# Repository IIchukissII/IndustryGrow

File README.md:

<!--
SPDX-FileCopyrightText: 2026 The IndustryGrow contributors
SPDX-License-Identifier: CC-BY-SA-4.0
-->

<picture>
  <source media="(prefers-color-scheme: dark)" srcset="img/industrygrow-logo-mono-dark.svg" />
  
</picture>

# IndustryGrow

Open-core field hardware, firmware and edge software for instrumented, profile-driven crop
cultivation. One architecture, from a cabinet to a several-hundred-square-metre facility. The
companion platform **IndustryFlow** stores history, runs analytics and distributes profiles.

Scope and rationale: [`MOTIVATION.md`](MOTIVATION.md), [ADR-0001](ADR/ADR-0001-industrygrow-as-an-open-core-cultivation-platform-on-industryflow.md).

## Architecture constraints

| Constraint | Record |
|---|---|
| Scaling multiplies node *instances* across zones. It adds no node classes. | ADR-0014 |
| A signed, versioned JSON cultivation profile is the only channel that changes deployment behaviour. There is no remote-command API and no real-time tuning channel. | ADR-0015, ADR-0025 |
| The gateway runs control loops locally against a cached profile. The cloud supplies profiles and observes; it does not command in real time. | ADR-0015, ADR-0004 |
| The over-temperature trip is analog, MCU- and bus-independent, and sits at the heating actuator. Profiles set operating parameters; hardware sets survival parameters. | ADR-0018 |
| Sensor density is a deployment phase, not a fixture: dense during the empirical survey, reduced for the operating phase. The profile carries the identified model with the setpoints. | ADR-0016 |

## Technology

| Layer | Choice |
|---|---|
| Field bus | Cyphal over classic CAN @ 500 kbit/s, linear topology |
| Smart-node MCU | WeAct STM32F4 64-pin core board (STM32F405RGT6; F412/F446 drop-in) |
| Node carrier PCB | Custom integration board: CAN transceiver, ATECC608 secure element, two-header sensor-module interface |
| Node firmware | Embedded C with libcanard. One application holds every module personality; the module-ID strap selects at boot |
| Node flash layout | Bootloader at the reset vector plus the application in one of two slots; build output is `igrowboot.hex`, `igrow-a.hex`, `igrow-b.hex` |
| Firmware update | Signed image served over the bus, `uavcan.file.Read` to the slot that is not running, trial boot with fallback |
| Gateway | Raspberry Pi (3B+ minimum, 4/5 for higher traffic) + isolated 2-channel CAN HAT |
| Gateway software | Python / asyncio, SocketCAN + Pycyphal + Nunavut-generated DSDL bindings |
| Cloud link | mTLS to IndustryFlow; stateless edge in steady state, with a bounded local store for buffering and survey |
| Identity | Module class from the ID strap, `unique_id` from the ATECC608, Node-ID from a carrier-resident store; 127 = unprovisioned |
| Security | Operator CA, signed firmware, signed profiles |

Governing records: ADR-0002 (bus, carrier, gateway), ADR-0005 (DSDL), ADR-0020
(persistence), ADR-0027 (identity), ADR-0029 (update and bootloader), ADR-0024 / ADR-0025 (CA,
profile signing).

> PCBs are authored in **KiCad 10** and will not open in earlier versions; cabinet distribution
> schematics (`E0007`) use **QElectroTech**. Design files live in `store/` under the ADR-0017
> scheme, packaged per document layer as `Exxxx-VVVVVV-S-src.zip` / `-D-src.zip` (d19).
> [`CONTRIBUTING.md`](CONTRIBUTING.md) has the unpack/repack procedure.

## Hardware

Seven sensor-module classes (M01–M07), one functional subsystem each, on the universal carrier
`E0001`, in the cabinet distribution case `E0007`. Instances of one design are specialized by
populated BOM, never by new designs; a functional group fitted or omitted at build is a populate
variant with its own assembly E-number (ADR-0017).

E-numbers, sensor complement, module-ID straps, variant rules and per-design state:
[`REGISTRY.md`](REGISTRY.md).

## Status

Phase 1 is data collection only, no actuators; it ends at stage 4, full cabinet telemetry from
M01–M05. Stage sequencing, dependencies, the Phase 1 → Phase 2 boundary and the v1.0 exit
criteria: [`project/ROADMAP.md`](project/ROADMAP.md), 14 dependency-ordered stages.

## Repository

| Path | Contents | Records |
|---|---|---|
| [`ADR/`](ADR/) | Architecture decision records — the source of truth — plus [`GLOSSARY.md`](ADR/GLOSSARY.md) | ADR-0000 |
| [`docs/`](docs/) | Decision manuals: how an ADR is realised and the code that realises it | — |
| [`REGISTRY.md`](REGISTRY.md) | E-number / SP-number identifier map, machine-readable | ADR-0017, ADR-0019, ADR-0023 |
| [`store/`](store/) | Hardware design sources, fab packages and firmware release artifacts, flat, keyed by identifier | ADR-0017 |
| [`spec/`](spec/) | Module specifications — M01, M02, M05, M06, M07. M03 and M04 not yet written | ADR-0014 |
| [`firmware/`](firmware/) | Node firmware (C, libcanard) and the `industryflow.greenhouse` DSDL vocabulary | ADR-0005, ADR-0029 |
| [`gateway/`](gateway/) | Gateway provisioning, hardening, identity and profile-pull client | ADR-0004, ADR-0015 |
| [`erp/`](erp/) | Instance-and-integration ERP — the pre-cloud system of record | ADR-0021, ADR-0022 |
| [`pki/`](pki/) | Operator CA bootstrap and root-key ceremony | ADR-0024 |
| [`signing/`](signing/) | Profile signing tool and runbook | ADR-0025 |
| [`profiles/`](profiles/) | Cultivation profile instances | ADR-0003 |
| [`project/`](project/) | `ROADMAP.md` stage plan, `RESEARCH.md` open directions L1–L7 | — |
| [`MOTIVATION.md`](MOTIVATION.md) | The gap this project closes | — |
| [`CONTRIBUTING.md`](CONTRIBUTING.md) | Contribution licensing, DCO sign-off, working with the store | — |

## Build and run

Firmware — three images, ARM cross-toolchain and Ninja required:

```sh
firmware/tools/bootstrap.sh            # pin submodules; needs nnvg (Nunavut)
cmake -S firmware -B firmware/build -G Ninja \
      -DCMAKE_MAKE_PROGRAM="$(command -v ninja)" \
      -DCMAKE_TOOLCHAIN_FILE="$PWD/firmware/cmake/arm-none-eabi.cmake"
cmake --build firmware/build
```

ERP — application plus operator console:

```sh
cd erp && docker compose up --build    # app on 127.0.0.1:8021
```

Gateway — runs on the Pi, post-first-boot, idempotent:

```sh
sudo ./provision.sh                    # from the staged gateway/ bundle
```

Per-component detail, flashing procedure and signing keys are in each directory's `README.md`.

## Licensing

Open-core, licensed per part of the repository. [`LICENSE.md`](LICENSE.md) is the authoritative
mapping — hardware designs, documentation, application code and the DSDL protocol layer carry four
different licences, and directory-level assumptions do not hold. Full texts are in
[`LICENSES/`](LICENSES/).

Third-party content keeps its own terms, annotated in [`REUSE.toml`](REUSE.toml): the WeAct
core-board snapshot is published with **no licence stated**, so it is not covered by this project's
licences. Compliance is CI-enforced — run `reuse lint` before opening a pull request.

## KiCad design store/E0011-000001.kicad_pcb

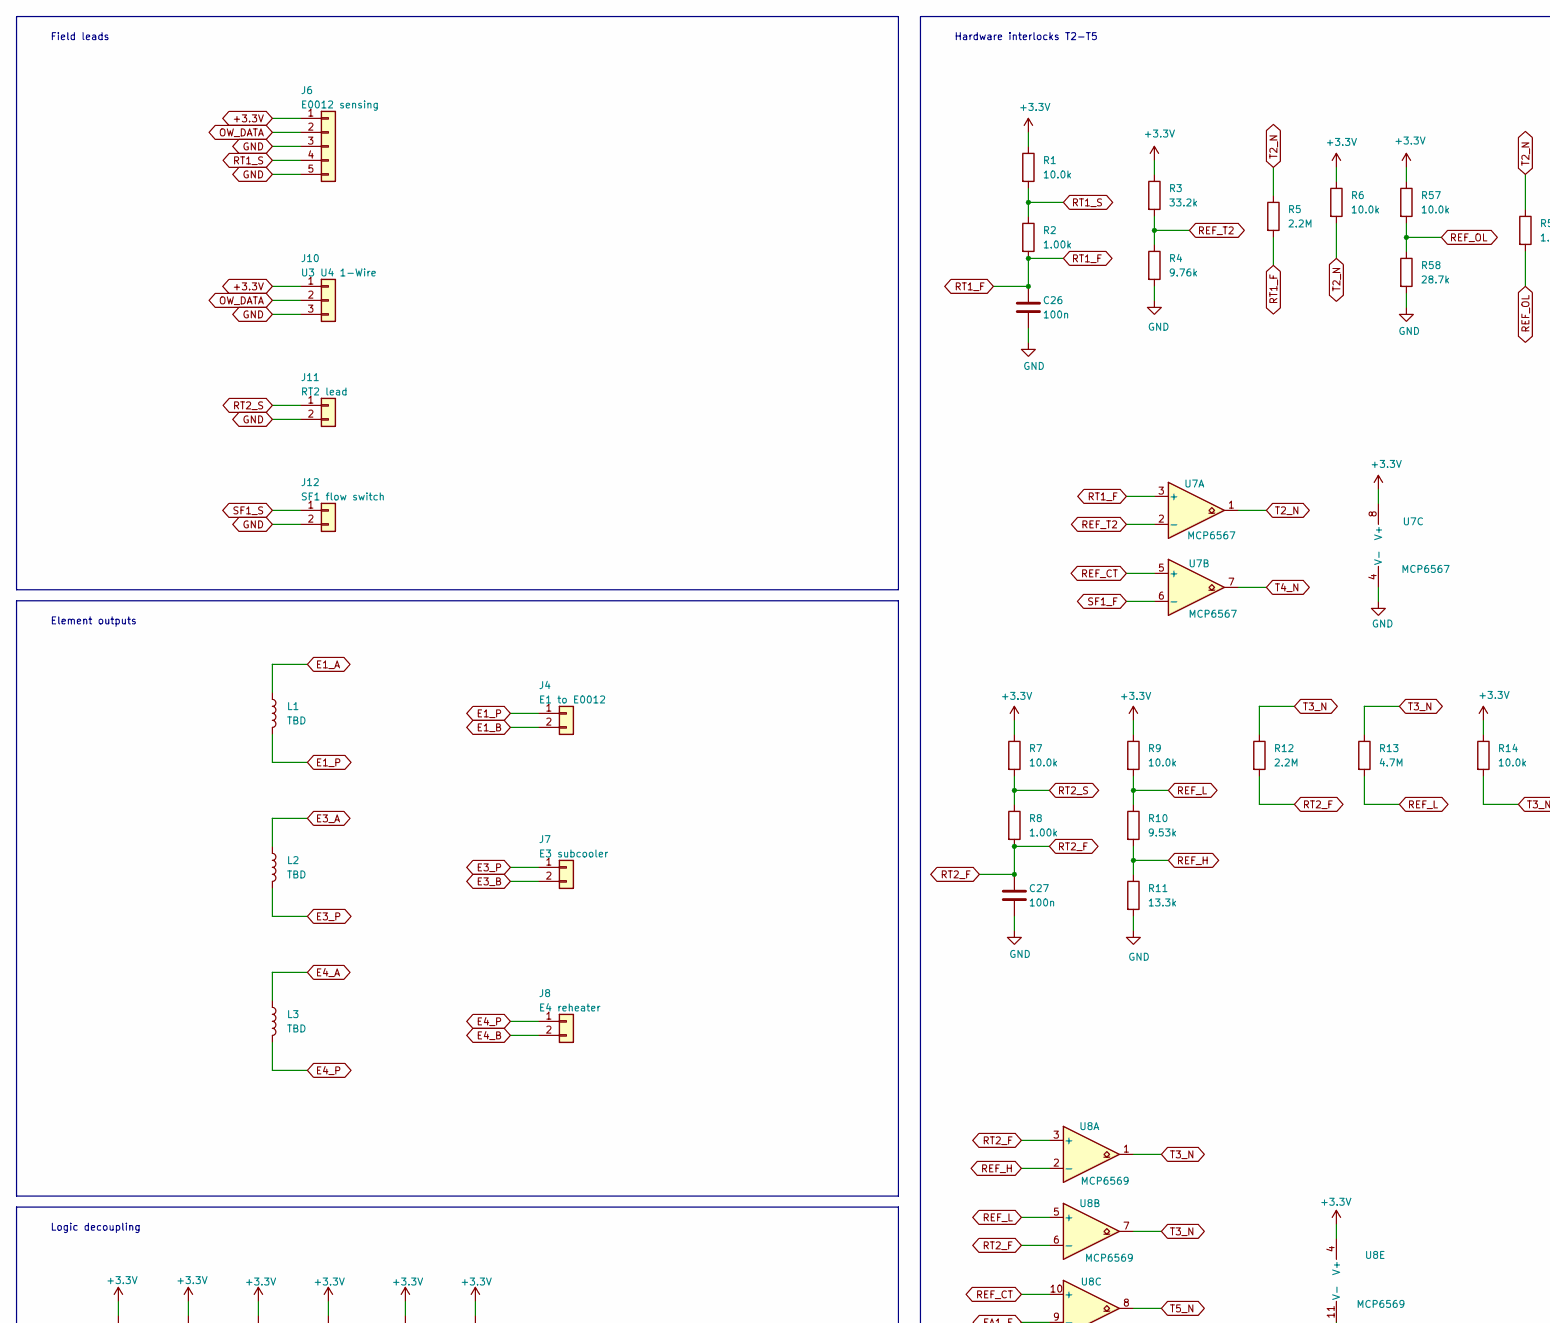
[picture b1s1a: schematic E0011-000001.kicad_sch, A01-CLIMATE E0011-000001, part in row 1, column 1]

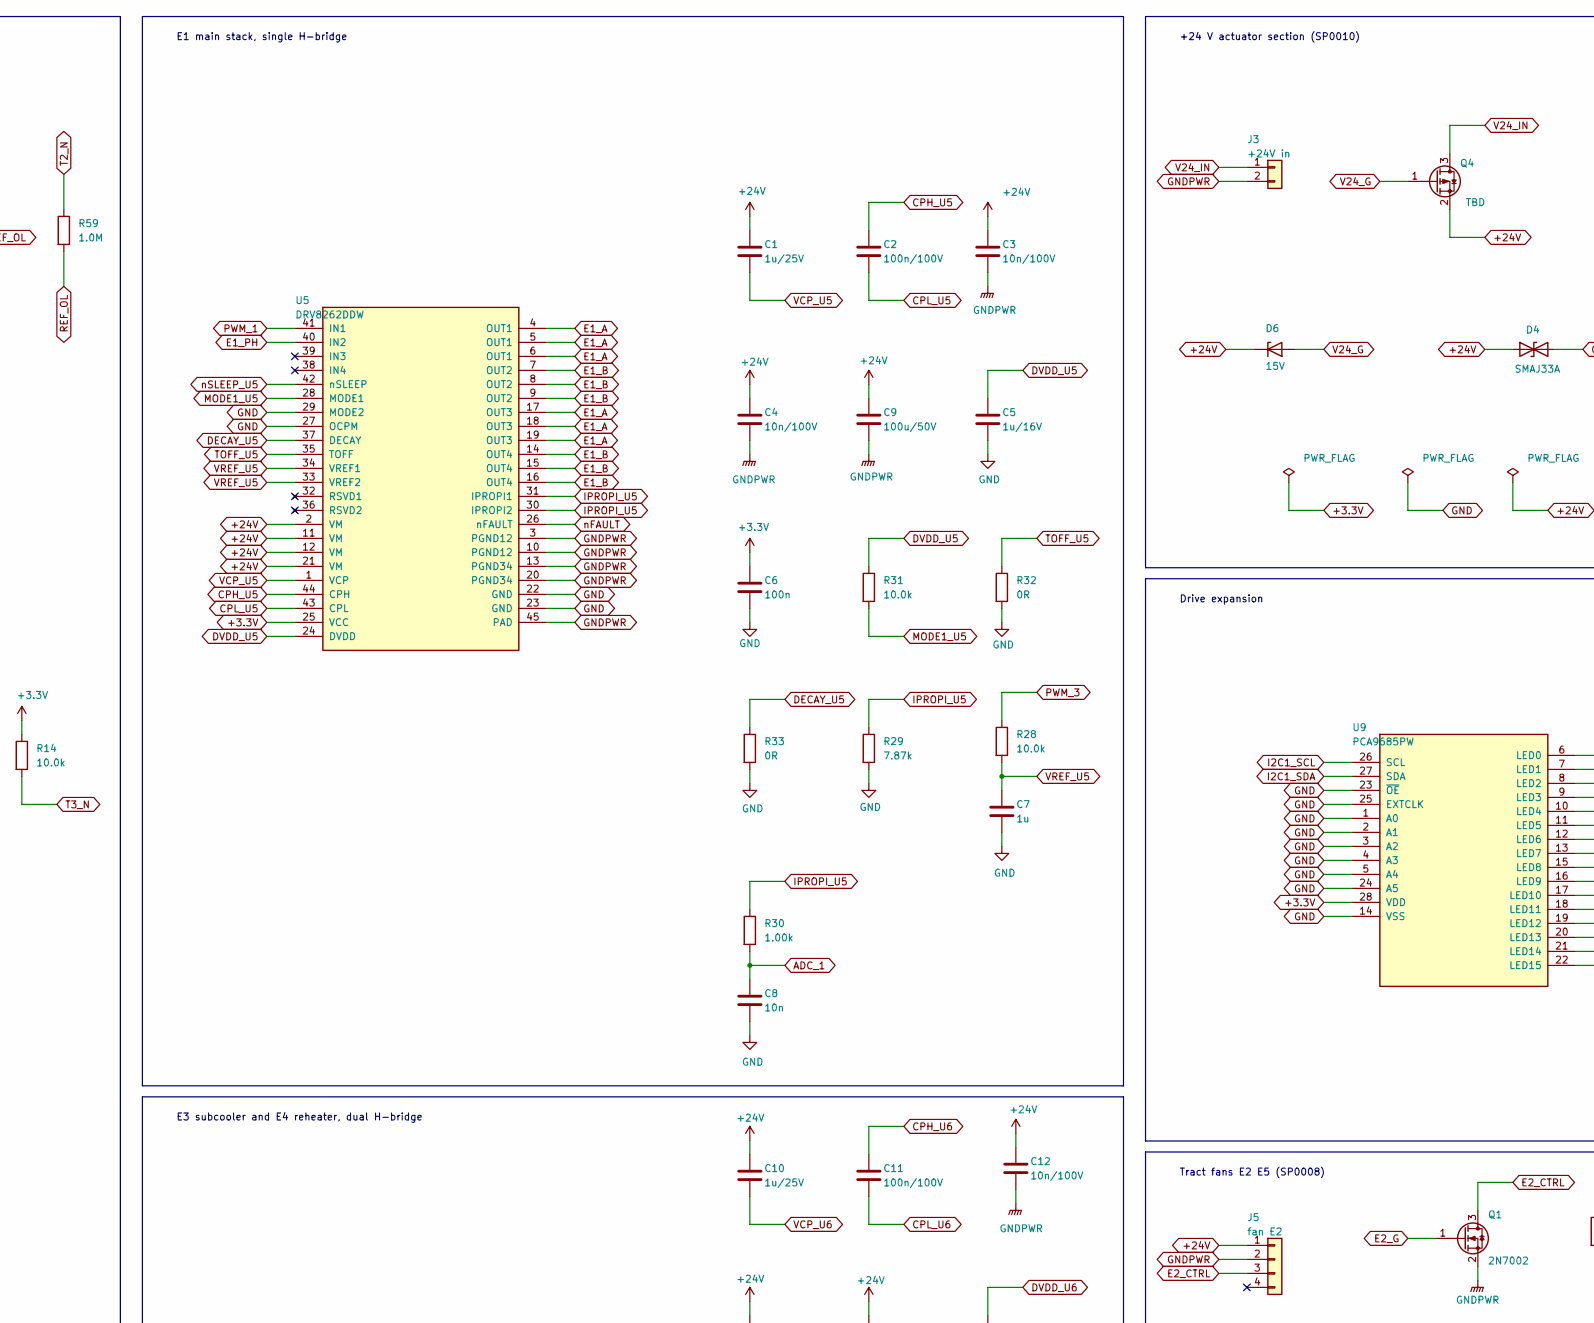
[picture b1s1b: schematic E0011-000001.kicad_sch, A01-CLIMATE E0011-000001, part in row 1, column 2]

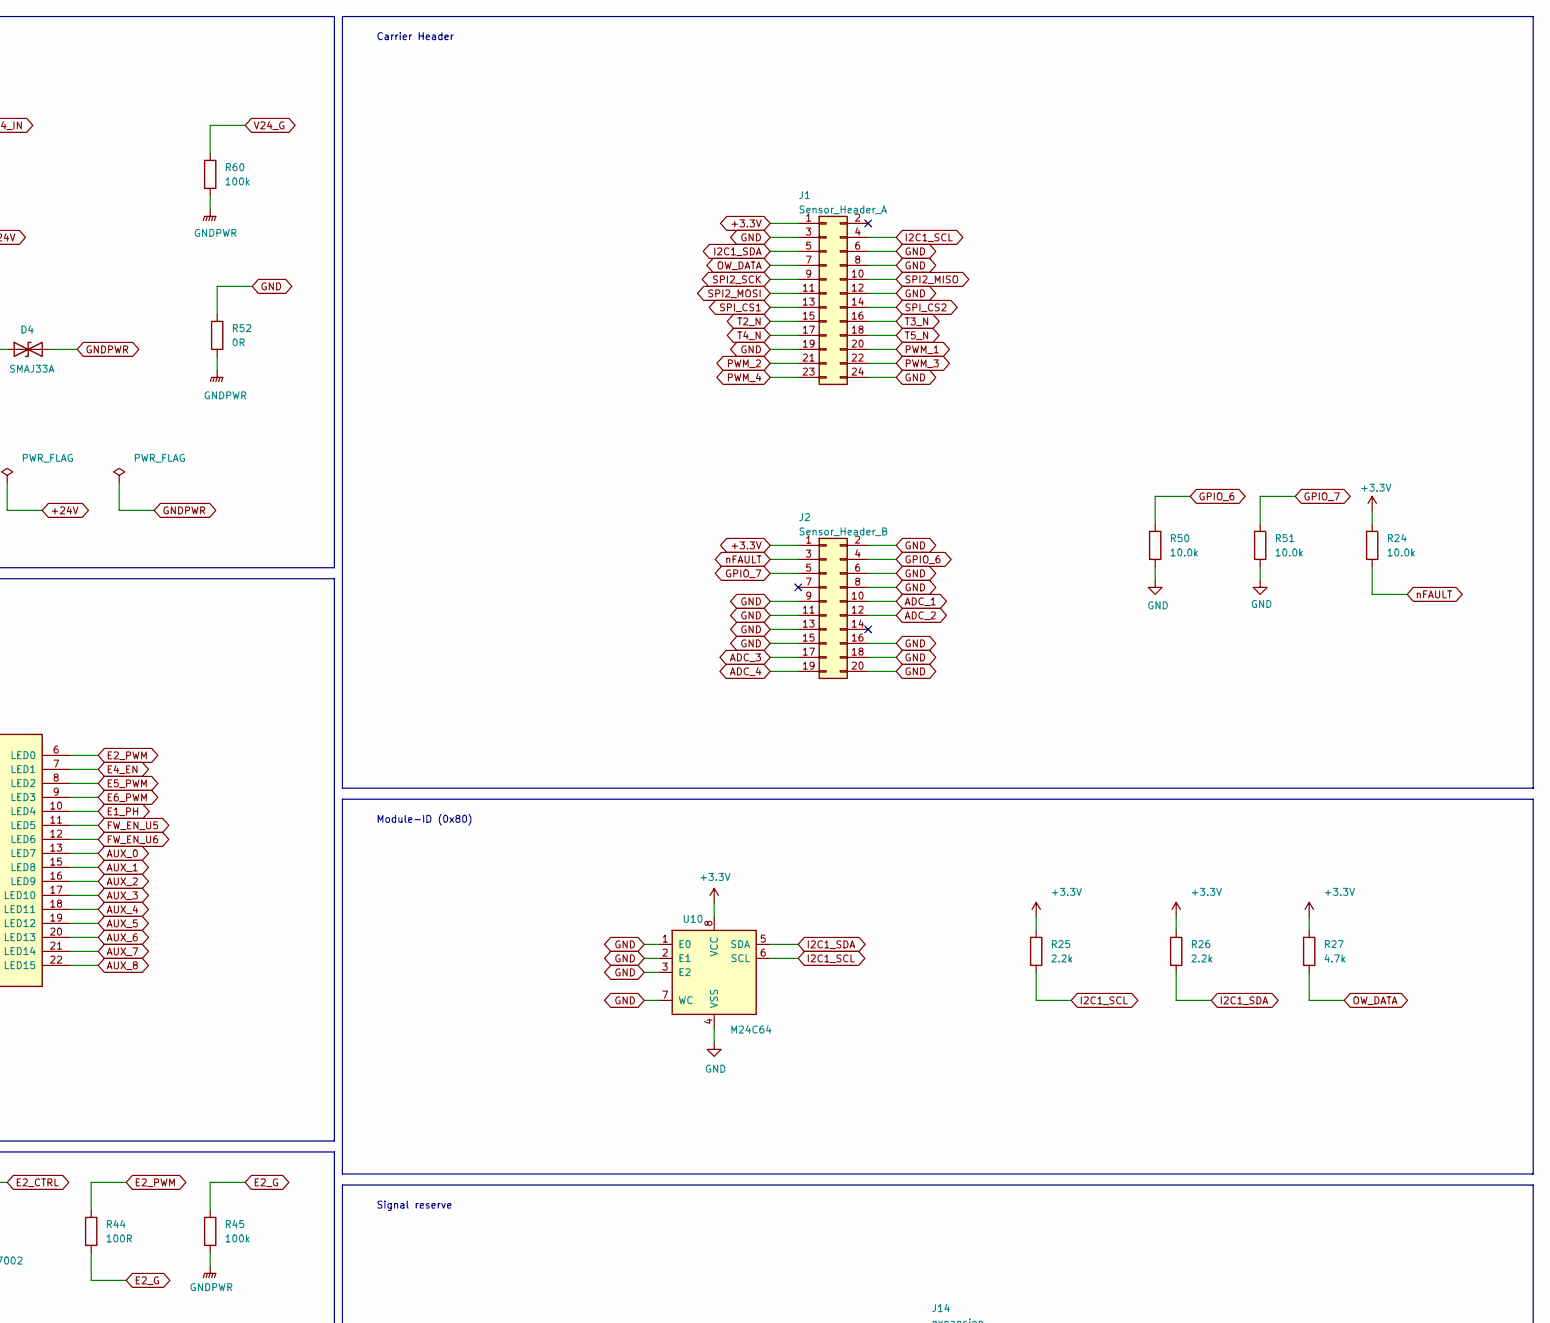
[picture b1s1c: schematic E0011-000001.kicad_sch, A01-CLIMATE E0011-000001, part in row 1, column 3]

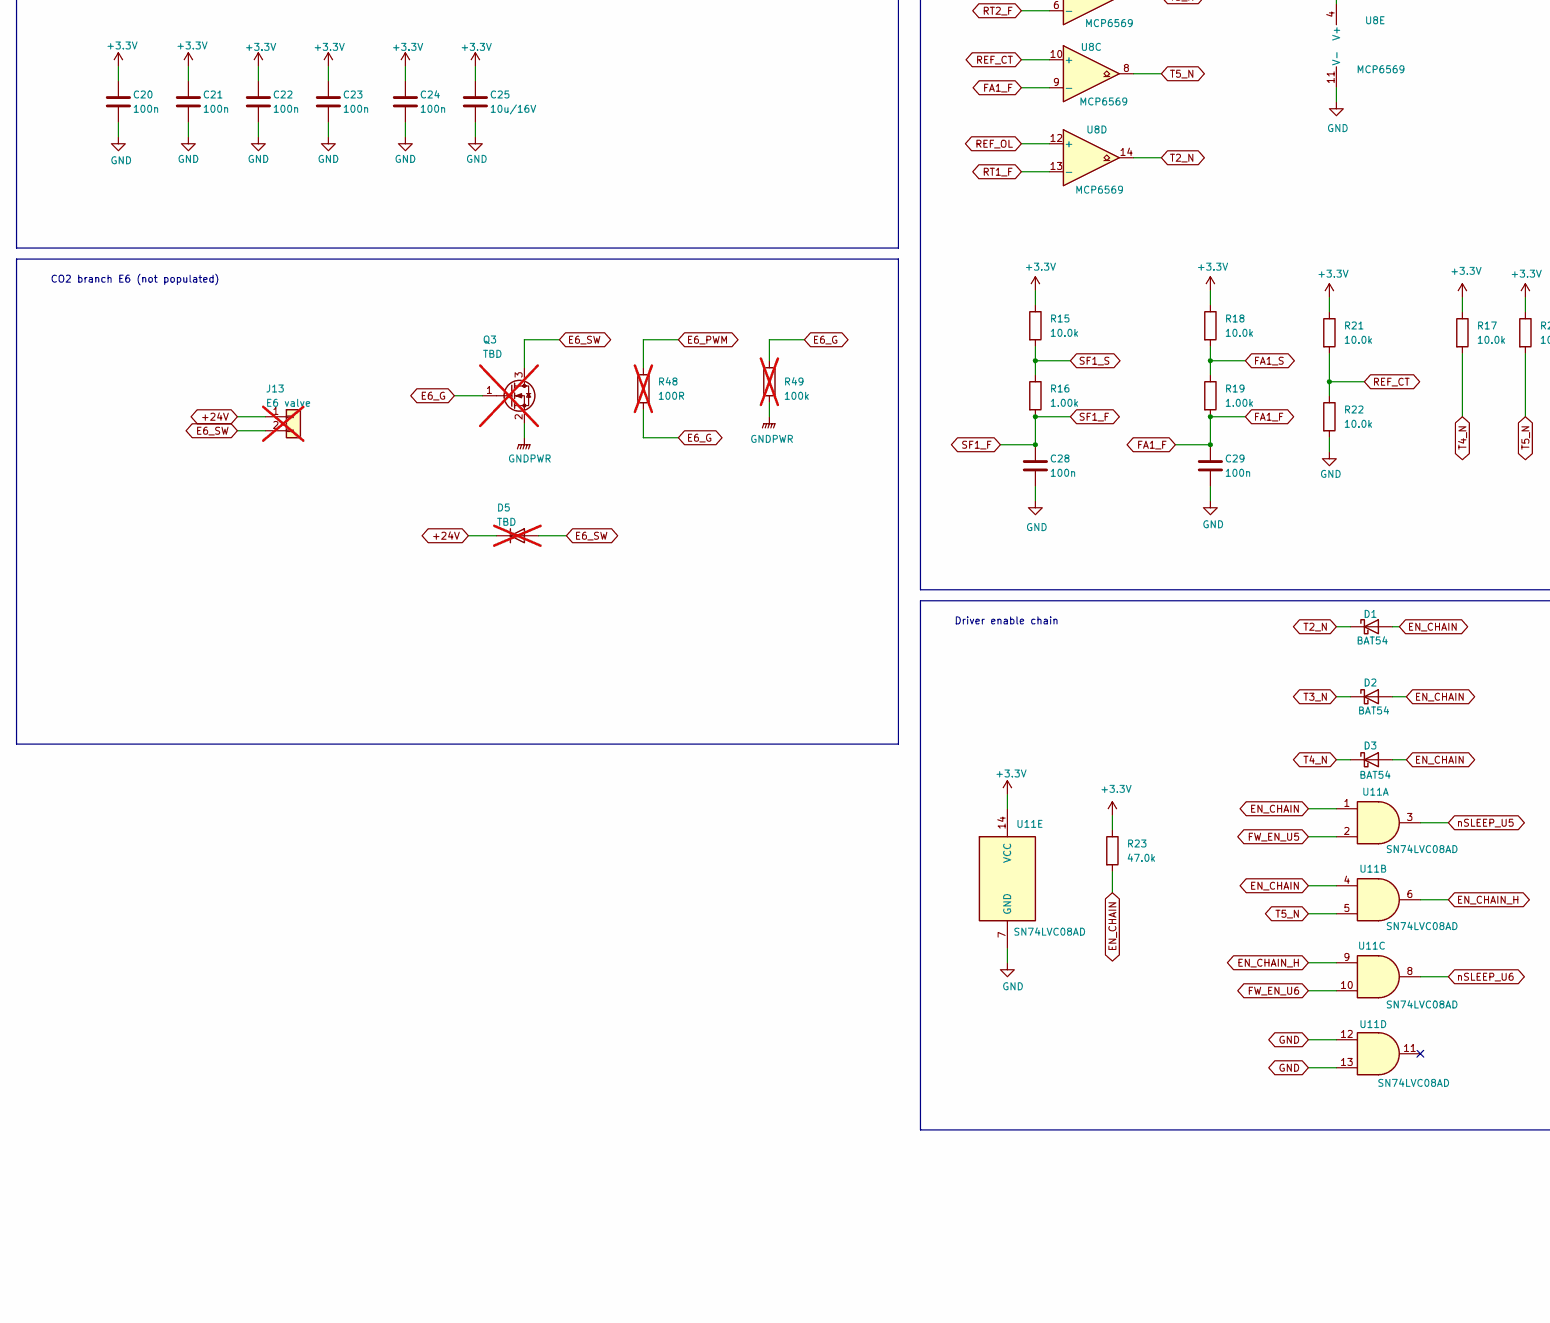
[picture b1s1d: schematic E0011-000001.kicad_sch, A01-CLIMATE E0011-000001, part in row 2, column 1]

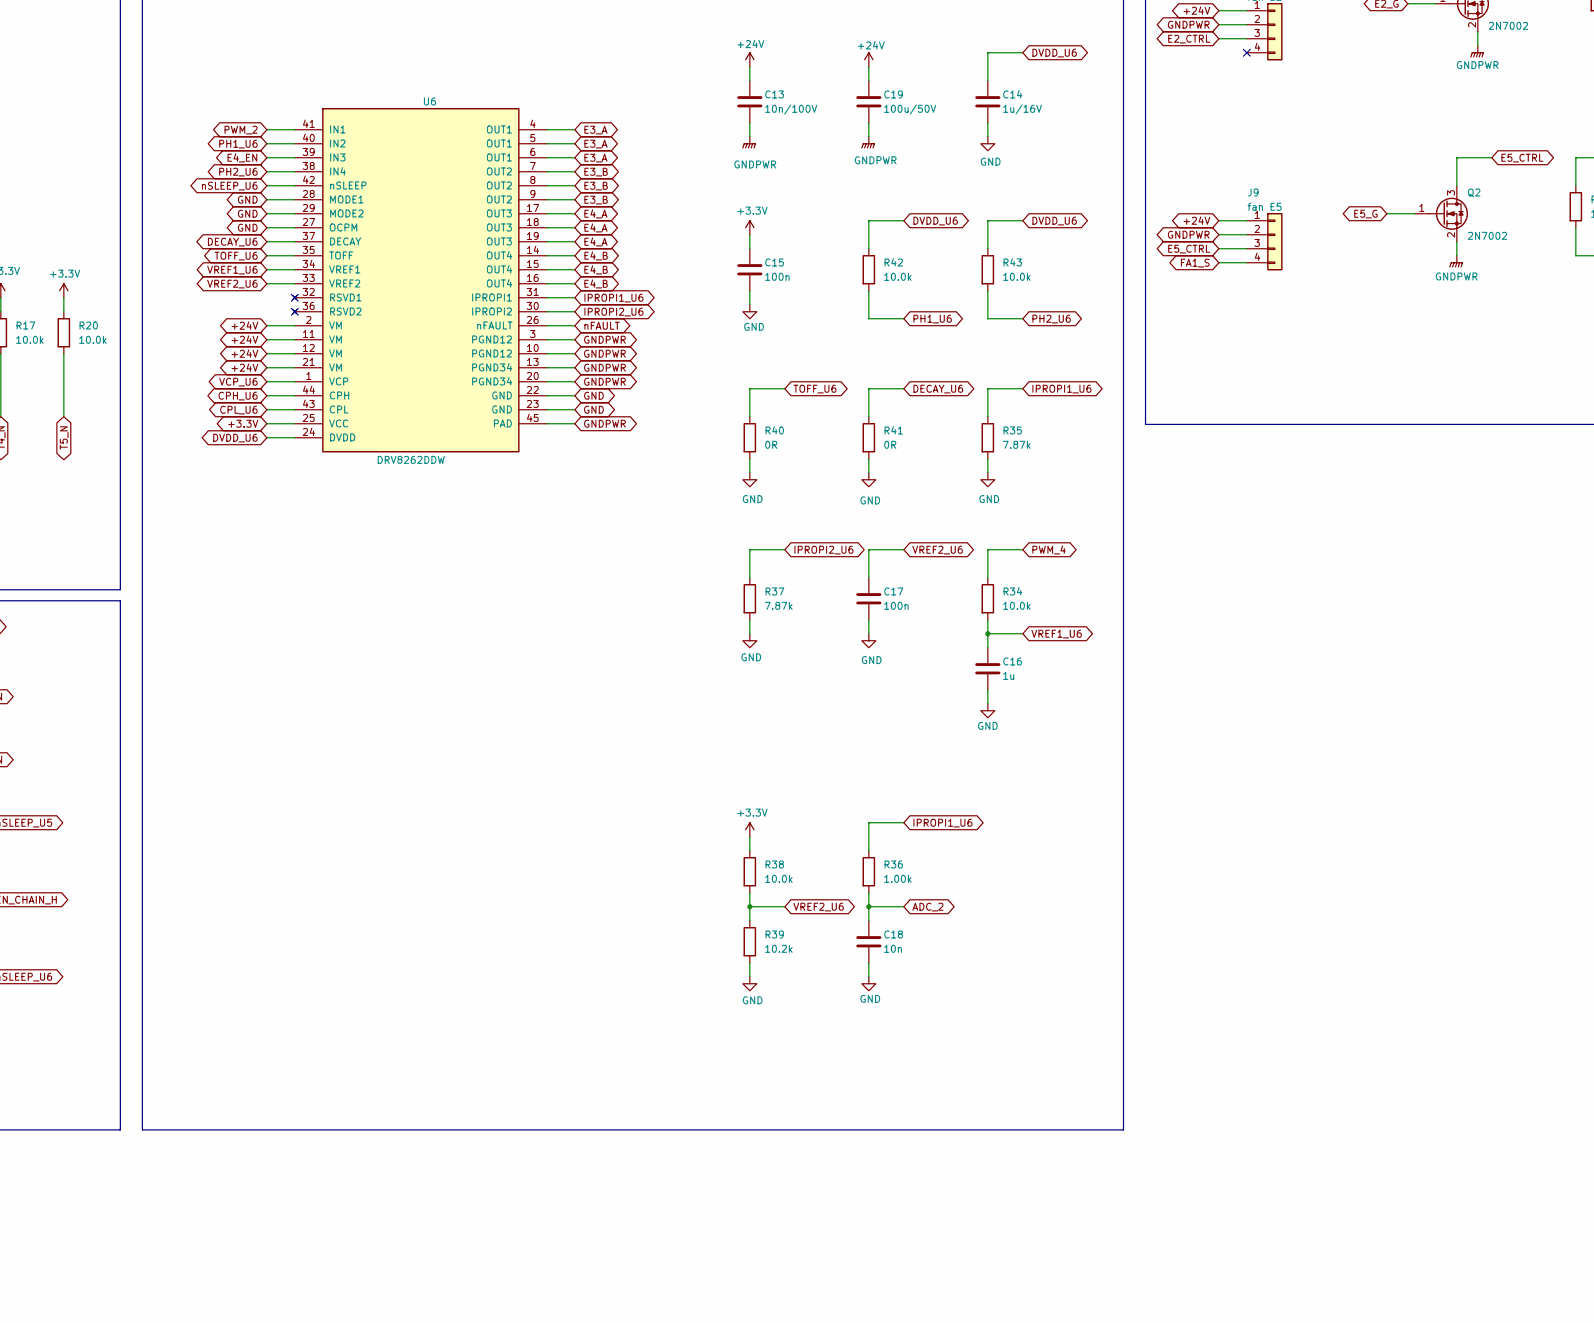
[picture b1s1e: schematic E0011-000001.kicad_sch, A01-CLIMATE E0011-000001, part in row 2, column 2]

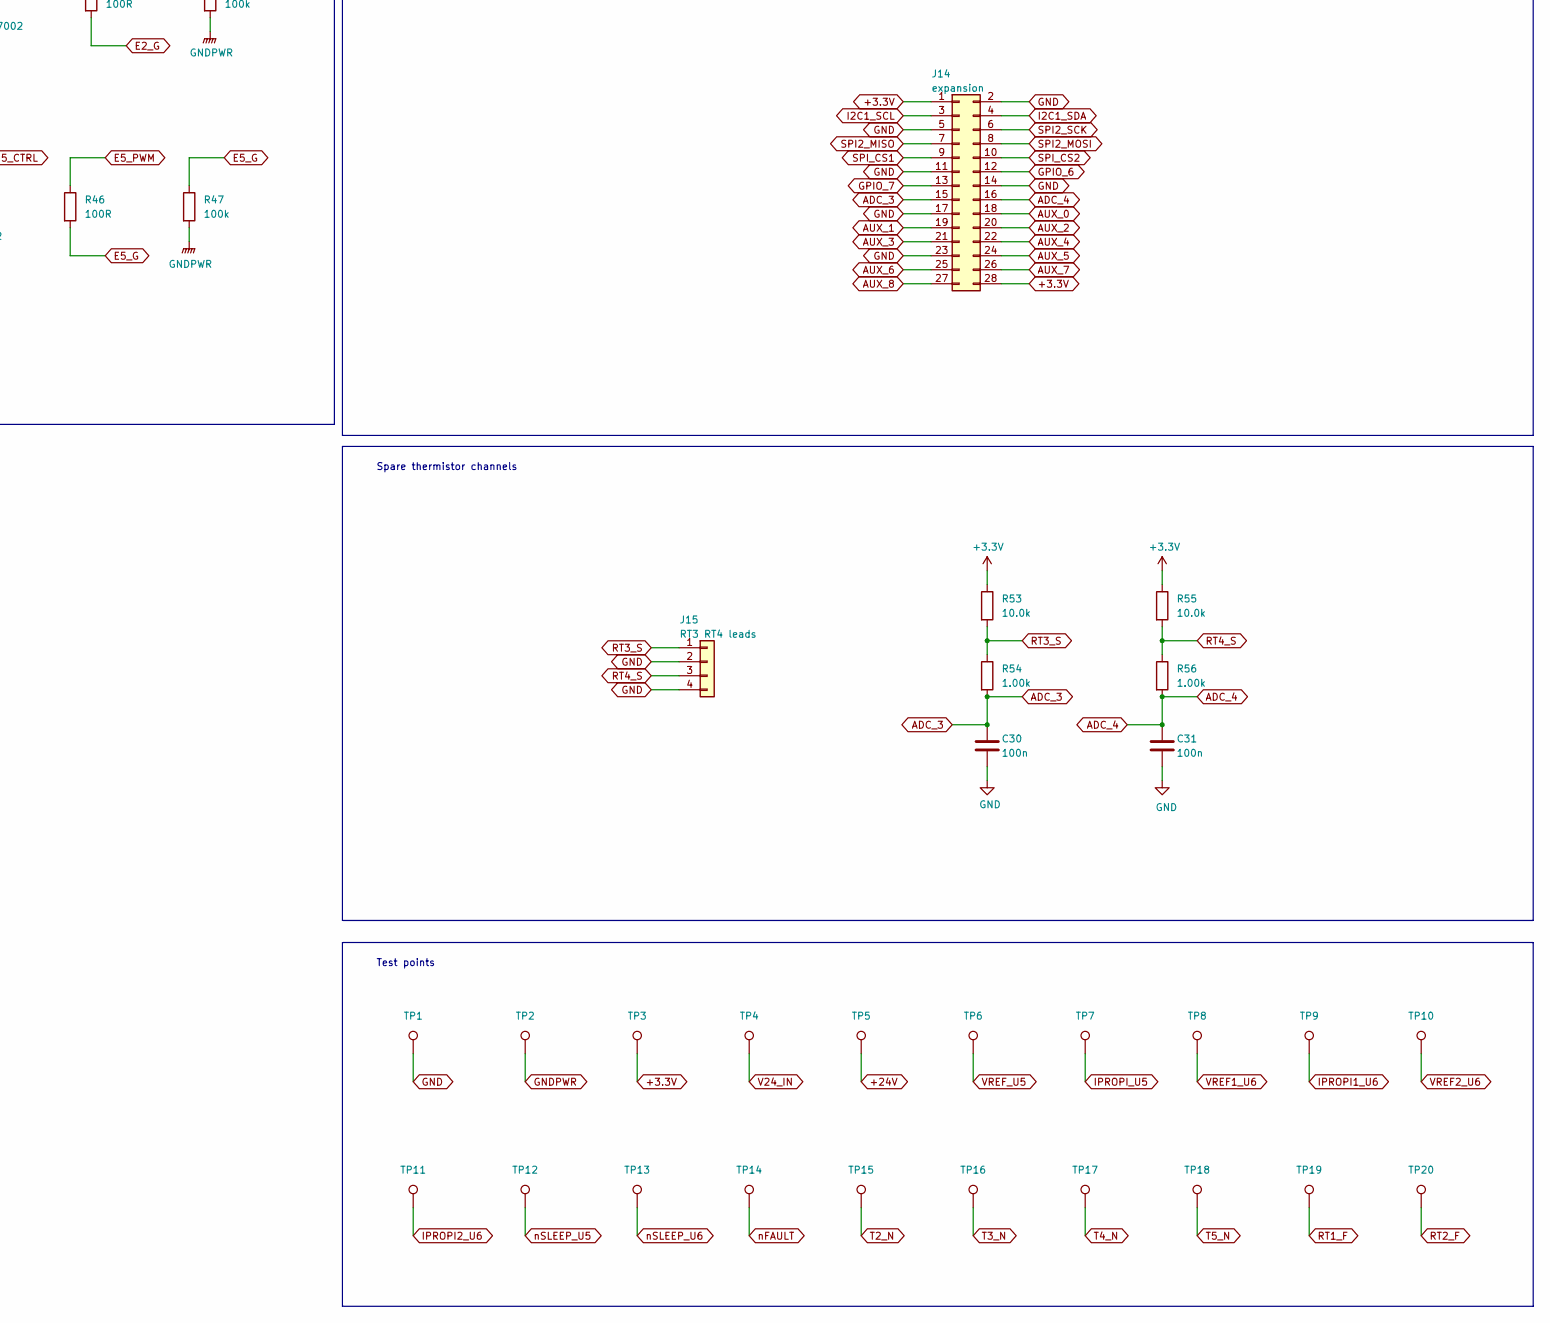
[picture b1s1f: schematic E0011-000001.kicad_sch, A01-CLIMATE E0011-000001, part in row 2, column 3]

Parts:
C1, C10: 1u/25V; C_0805_2012Metric
C2: 100n/100V; C_0805_2012Metric
C3, C4, C12, C13: 10n/100V; C_0805_2012Metric
C5, C14: 1u/16V; C_0805_2012Metric
C6, C15, C17, C20, C21, C22, C23, C24, C26, C27, C28, C29, C30, C31: 100n; C_0805_2012Metric
C7, C16: 1u; C_0805_2012Metric
C8, C18: 10n; C_0805_2012Metric
C9, C19: 100u/50V; CP_Elec_8x10.5
C11: 100n/100V; C_0603_1608Metric
C25: 10u/16V; C_0805_2012Metric
D1, D2, D3: BAT54; D_SOD-123
D4: SMAJ33A; D_SMA
D5: TBD; D_SOD-123; not fitted
D6: 15V; D_SOD-123
J1: Sensor_Header_A; PinHeader_2x12_P2.54mm_Vertical
J2: Sensor_Header_B; PinHeader_2x10_P2.54mm_Vertical
J3: +24V in; TerminalBlock_Phoenix_MKDS-1,5-2_1x02_P5.00mm_Horizontal
J4: E1 to E0012; TerminalBlock_Phoenix_MKDS-1,5-2_1x02_P5.00mm_Horizontal
J5: fan E2; Molex_Micro-Fit_3.0_43650-0400_1x04_P3.00mm_Horizontal
J6: E0012 sensing; Molex_Micro-Fit_3.0_43650-0500_1x05_P3.00mm_Horizontal
J7: E3 subcooler; TerminalBlock_Phoenix_MKDS-1,5-2_1x02_P5.00mm_Horizontal
J8: E4 reheater; TerminalBlock_Phoenix_MKDS-1,5-2_1x02_P5.00mm_Horizontal
J9: fan E5; Molex_Micro-Fit_3.0_43650-0400_1x04_P3.00mm_Horizontal
J10: U3 U4 1-Wire; Molex_Micro-Fit_3.0_43650-0300_1x03_P3.00mm_Horizontal
J11: RT2 lead; Molex_Micro-Fit_3.0_43650-0200_1x02_P3.00mm_Horizontal
J12: SF1 flow switch; Molex_Micro-Fit_3.0_43650-0200_1x02_P3.00mm_Horizontal
J13: E6 valve; TerminalBlock_Phoenix_MKDS-1,5-2_1x02_P5.00mm_Horizontal; not fitted
J14: expansion; PinHeader_2x14_P2.54mm_Vertical
J15: RT3 RT4 leads; Molex_Micro-Fit_3.0_43650-0400_1x04_P3.00mm_Horizontal
L1, L2, L3: TBD; L_12x12mm_H8mm
Q1, Q2: 2N7002; SOT-23
Q3: TBD; SOT-23; not fitted
Q4: TBD; SOT-23
R1, R6, R7, R9, R14, R15, R17, R18, R20, R21, R22, R24, R28, R43, R50, R51, R53, R55, R57: 10.0k; R_0805_2012Metric
R2, R8, R16, R19, R54, R56: 1.00k; R_0805_2012Metric
R3: 33.2k; R_0805_2012Metric
R4: 9.76k; R_0805_2012Metric
R5, R12: 2.2M; R_0805_2012Metric
R10: 9.53k; R_0805_2012Metric
R11: 13.3k; R_0805_2012Metric
R13: 4.7M; R_0805_2012Metric
R23: 47.0k; R_0805_2012Metric
R25, R26: 2.2k; R_0805_2012Metric
R27: 4.7k; R_0805_2012Metric
R29, R35, R37: 7.87k; R_0603_1608Metric
R30, R36: 1.00k; R_0603_1608Metric
R31, R34, R38, R42: 10.0k; R_0603_1608Metric
R32, R33, R40, R41: 0R; R_0603_1608Metric
R39: 10.2k; R_0603_1608Metric
R44, R46: 100R; R_0805_2012Metric
R45, R47, R60: 100k; R_0805_2012Metric
R48: 100R; R_0805_2012Metric; not fitted
R49: 100k; R_0805_2012Metric; not fitted
R52: 0R; R_0805_2012Metric
R58: 28.7k; R_0805_2012Metric
R59: 1.0M; R_0805_2012Metric
TP1, TP2, TP3, TP4, TP5, TP6, TP7, TP8, TP9, TP10, TP11, TP12, TP13, TP14, TP15, TP16, TP17, TP18, TP19, TP20: TestPoint; TestPoint_Pad_D1.5mm
U5, U6: DRV8262DDW; HTSSOP-44-1EP_6.1x14mm_P0.635mm_EP5.2x14mm_Mask4.31x8.26mm_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
U7: MCP6567; SOIC-8_3.9x4.9mm_P1.27mm
U8: MCP6569; SOIC-14_3.9x8.7mm_P1.27mm
U9: PCA9685PW; TSSOP-28_4.4x9.7mm_P0.65mm
U10: M24C64; SOIC-8_3.9x4.9mm_P1.27mm
U11: SN74LVC08AD; SOIC-14_3.9x8.7mm_P1.27mm

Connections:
+3.3V: C6.1, C15.1, C20.1, C21.1, C22.1, C23.1, C24.1, C25.1, J1.1, J2.1, J6.1, J10.1, J14.1, J14.28, R1.1, R3.1, R6.1, R7.1, R9.1, R14.1, R15.1, R17.1, R18.1, R20.1, R21.1, R23.1, R24.1, R25.1, R26.1, R27.1, R38.1, R53.1, R55.1, R57.1, TP3.1, U5.25 (VCC), U6.25 (VCC), U7.8 (V+), U8.4 (V+), U9.28 (VDD), U10.8 (VCC), U11.14 (VCC)
+24V: C1.1, C3.1, C4.1, C9.1, C10.1, C12.1, C13.1, C19.1, D4.1 (A1), D5.1 (K), D6.1 (K), J5.1, J9.1, J13.1, Q4.2 (S), TP5.1, U5.2 (VM), U5.11 (VM), U5.12 (VM), U5.21 (VM), U6.2 (VM), U6.11 (VM), U6.12 (VM), U6.21 (VM)
ADC_1: C8.1, J2.10, R30.2
ADC_2: C18.1, J2.12, R36.2
ADC_3: C30.1, J2.17, J14.15, R54.2
ADC_4: C31.1, J2.19, J14.16, R56.2
AUX_0: J14.18, U9.13 (LED7)
AUX_1: J14.19, U9.15 (LED8)
AUX_2: J14.20, U9.16 (LED9)
AUX_3: J14.21, U9.17 (LED10)
AUX_4: J14.22, U9.18 (LED11)
AUX_5: J14.24, U9.19 (LED12)
AUX_6: J14.25, U9.20 (LED13)
AUX_7: J14.26, U9.21 (LED14)
AUX_8: J14.27, U9.22 (LED15)
CPH_U5: C2.1, U5.44 (CPH)
CPH_U6: C11.1, U6.44 (CPH)
CPL_U5: C2.2, U5.43 (CPL)
CPL_U6: C11.2, U6.43 (CPL)
DECAY_U5: R33.1, U5.37 (DECAY)
DECAY_U6: R41.1, U6.37 (DECAY)
DVDD_U5: C5.1, R31.1, U5.24 (DVDD)
DVDD_U6: C14.1, R42.1, R43.1, U6.24 (DVDD)
E1_A: L1.1, U5.4 (OUT1), U5.5 (OUT1), U5.6 (OUT1), U5.17 (OUT3), U5.18 (OUT3), U5.19 (OUT3)
E1_B: J4.2, U5.7 (OUT2), U5.8 (OUT2), U5.9 (OUT2), U5.14 (OUT4), U5.15 (OUT4), U5.16 (OUT4)
E1_P: J4.1, L1.2
E1_PH: U5.40 (IN2), U9.10 (LED4)
E2_CTRL: J5.3, Q1.3 (D)
E2_G: Q1.1 (G), R44.2, R45.1
E2_PWM: R44.1, U9.6 (LED0)
E3_A: L2.1, U6.4 (OUT1), U6.5 (OUT1), U6.6 (OUT1)
E3_B: J7.2, U6.7 (OUT2), U6.8 (OUT2), U6.9 (OUT2)
E3_P: J7.1, L2.2
E4_A: L3.1, U6.17 (OUT3), U6.18 (OUT3), U6.19 (OUT3)
E4_B: J8.2, U6.14 (OUT4), U6.15 (OUT4), U6.16 (OUT4)
E4_EN: U6.39 (IN3), U9.7 (LED1)
E4_P: J8.1, L3.2
E5_CTRL: J9.3, Q2.3 (D)
E5_G: Q2.1 (G), R46.2, R47.1
E5_PWM: R46.1, U9.8 (LED2)
E6_G: Q3.1 (G), R48.2, R49.1
E6_PWM: R48.1, U9.9 (LED3)
E6_SW: D5.2 (A), J13.2, Q3.3 (D)
EN_CHAIN: D1.2 (A), D2.2 (A), D3.2 (A), R23.2, U11.1, U11.4
EN_CHAIN_H: U11.6, U11.9
FA1_F: C29.1, R19.2, U8.9 (-)
FA1_S: J9.4, R18.2, R19.1
FW_EN_U5: U9.11 (LED5), U11.2
FW_EN_U6: U9.12 (LED6), U11.10
GND: C5.2, C6.2, C7.2, C8.2, C14.2, C15.2, C16.2, C17.2, C18.2, C20.2, C21.2, C22.2, C23.2, C24.2, C25.2, C26.2, C27.2, C28.2, C29.2, C30.2, C31.2, J1.3, J1.6, J1.8, J1.12, J1.19, J1.24, J2.2, J2.6, J2.8, J2.9, J2.11, J2.13, J2.15, J2.16, J2.18, J2.20, J6.3, J6.5, J10.3, J11.2, J12.2, J14.2, J14.5, J14.11, J14.14, J14.17, J14.23, J15.2, J15.4, R4.2, R11.2, R22.2, R29.2, R32.2, R33.2, R35.2, R37.2, R39.2, R40.2, R41.2, R50.2, R51.2, R52.1, R58.2, TP1.1, U5.22 (GND), U5.23 (GND), U5.27 (OCPM), U5.29 (MODE2), U6.22 (GND), U6.23 (GND), U6.27 (OCPM), U6.28 (MODE1), U6.29 (MODE2), U7.4 (V-), U8.11 (V-), U9.1 (A0), U9.2 (A1), U9.3 (A2), U9.4 (A3), U9.5 (A4), U9.14 (VSS), U9.23 (~OE), U9.24 (A5), U9.25 (EXTCLK), U10.1 (E0), U10.2 (E1), U10.3 (E2), U10.4 (VSS), U10.7 (WC), U11.7 (GND), U11.12, U11.13
GNDPWR: C3.2, C4.2, C9.2, C12.2, C13.2, C19.2, D4.2 (A2), J3.2, J5.2, J9.2, Q1.2 (S), Q2.2 (S), Q3.2 (S), R45.2, R47.2, R49.2, R52.2, R60.2, TP2.1, U5.3 (PGND12), U5.10 (PGND12), U5.13 (PGND34), U5.20 (PGND34), U5.45 (PAD), U6.3 (PGND12), U6.10 (PGND12), U6.13 (PGND34), U6.20 (PGND34), U6.45 (PAD)
GPIO_6: J2.4, J14.12, R50.1
GPIO_7: J2.5, J14.13, R51.1
I2C1_SCL: J1.4, J14.3, R25.2, U9.26 (SCL), U10.6 (SCL)
I2C1_SDA: J1.5, J14.4, R26.2, U9.27 (SDA), U10.5 (SDA)
IPROPI1_U6: R35.1, R36.1, TP9.1, U6.31 (IPROPI1)
IPROPI2_U6: R37.1, TP11.1, U6.30 (IPROPI2)
IPROPI_U5: R29.1, R30.1, TP7.1, U5.30 (IPROPI2), U5.31 (IPROPI1)
MODE1_U5: R31.2, U5.28 (MODE1)
OW_DATA: J1.7, J6.2, J10.2, R27.2
PH1_U6: R42.2, U6.40 (IN2)
PH2_U6: R43.2, U6.38 (IN4)
PWM_1: J1.20, U5.41 (IN1)
PWM_2: J1.21, U6.41 (IN1)
PWM_3: J1.22, R28.1
PWM_4: J1.23, R34.1
REF_CT: R21.2, R22.1, U7.5 (+), U8.10 (+)
REF_H: R10.2, R11.1, U8.2 (-)
REF_L: R9.2, R10.1, R13.2, U8.5 (+)
REF_OL: R57.2, R58.1, R59.2, U8.12 (+)
REF_T2: R3.2, R4.1, U7.2 (-)
RT1_F: C26.1, R2.2, R5.2, TP19.1, U7.3 (+), U8.13 (-)
RT1_S: J6.4, R1.2, R2.1
RT2_F: C27.1, R8.2, R12.2, TP20.1, U8.3 (+), U8.6 (-)
RT2_S: J11.1, R7.2, R8.1
RT3_S: J15.1, R53.2, R54.1
RT4_S: J15.3, R55.2, R56.1
SF1_F: C28.1, R16.2, U7.6 (-)
SF1_S: J12.1, R15.2, R16.1
SPI2_MISO: J1.10, J14.7
SPI2_MOSI: J1.11, J14.8
SPI2_SCK: J1.9, J14.6
SPI_CS1: J1.13, J14.9
SPI_CS2: J1.14, J14.10
T2_N: D1.1 (K), J1.15, R5.1, R6.2, R59.1, TP15.1, U7.1, U8.14
T3_N: D2.1 (K), J1.16, R12.1, R13.1, R14.2, TP16.1, U8.1, U8.7
T4_N: D3.1 (K), J1.17, R17.2, TP17.1, U7.7
T5_N: J1.18, R20.2, TP18.1, U8.8, U11.5
TOFF_U5: R32.1, U5.35 (TOFF)
TOFF_U6: R40.1, U6.35 (TOFF)
V24_G: D6.2 (A), Q4.1 (G), R60.1
V24_IN: J3.1, Q4.3 (D), TP4.1
VCP_U5: C1.2, U5.1 (VCP)
VCP_U6: C10.2, U6.1 (VCP)
VREF1_U6: C16.1, R34.2, TP8.1, U6.34 (VREF1)
VREF2_U6: C17.1, R38.2, R39.1, TP10.1, U6.33 (VREF2)
VREF_U5: C7.1, R28.2, TP6.1, U5.33 (VREF2), U5.34 (VREF1)
nFAULT: J2.3, R24.2, TP14.1, U5.26 (nFAULT), U6.26 (nFAULT)
nSLEEP_U5: TP12.1, U5.42 (nSLEEP), U11.3
nSLEEP_U6: TP13.1, U6.42 (nSLEEP), U11.8

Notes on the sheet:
Logic decoupling
Field leads
Tract fans E2 E5 (SP0008)
E1 main stack, single H-bridge
CO2 branch E6 (not populated)
+24 V actuator section (SP0010)
Element outputs
Hardware interlocks T2-T5
Signal reserve
E3 subcooler and E4 reheater, dual H-bridge
Driver enable chain
Module-ID (0x80)
Carrier Header
Spare thermistor channels
Drive expansion
Test points

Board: 4 copper layers, 146 parts (20 on the bottom side), 100 nets, no tracks yet.
